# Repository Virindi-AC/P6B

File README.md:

# P6B
A Ramps-like printer board with 8 stepper drivers, 5 mosfets, and TMC2130 SPI.

By Jessica "Virindi" O.

pin_P6B.h is the pin configuration for Marlin.

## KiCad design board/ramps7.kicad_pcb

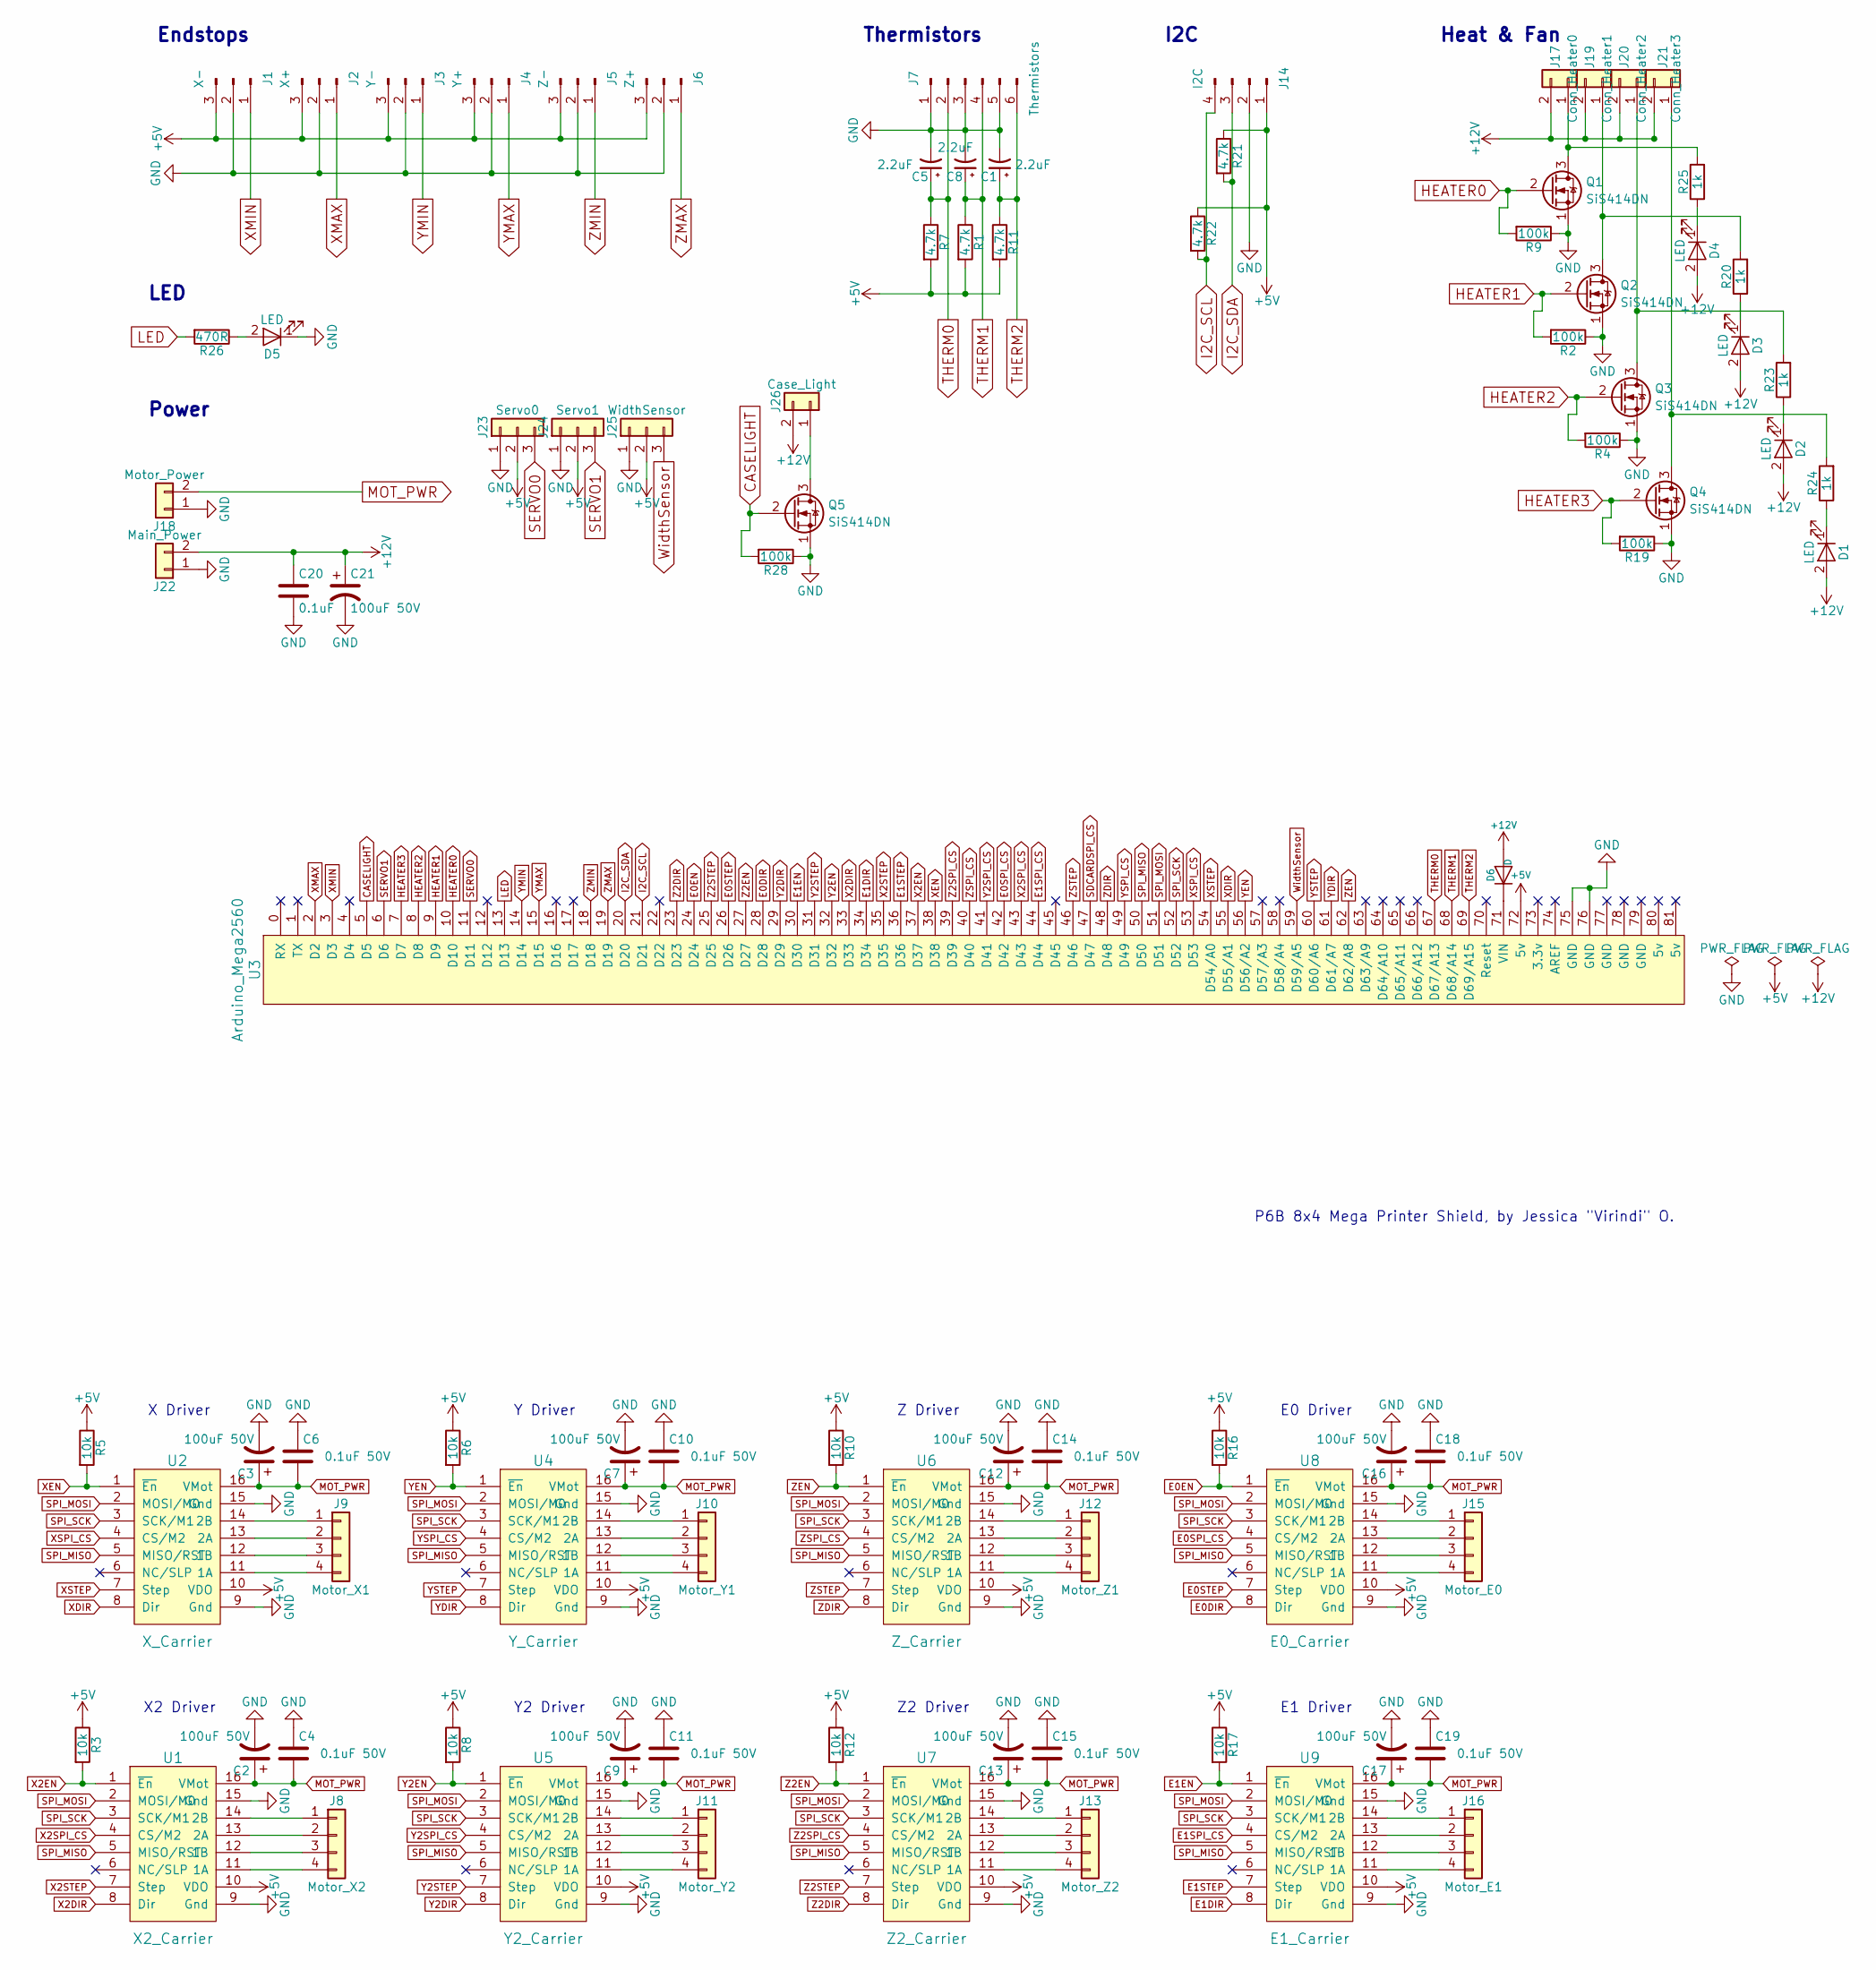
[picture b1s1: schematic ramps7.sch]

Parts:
C1, C5, C8: 2.2uF; C_0805
C2, C3, C7, C9, C12, C13, C16, C17, C21: 100uF 50V; CP_Elec_10x10.5
C4, C6, C10, C11, C14, C15, C18, C19: 0.1uF 50V; C_0805
C20: 0.1uF; C_0805
D1, D2, D3, D4, D5: LED; LED_0805
D6: D; D_DO-35_SOD27_P7.62mm_Horizontal
J1: X-; Pin_Header_Straight_1x03_Pitch2.54mm_SMD_Pin1Right
J2: X+; Pin_Header_Straight_1x03_Pitch2.54mm_SMD_Pin1Right
J3: Y-; Pin_Header_Straight_1x03_Pitch2.54mm_SMD_Pin1Right
J4: Y+; Pin_Header_Straight_1x03_Pitch2.54mm_SMD_Pin1Right
J5: Z-; Pin_Header_Straight_1x03_Pitch2.54mm_SMD_Pin1Right
J6: Z+; Pin_Header_Straight_1x03_Pitch2.54mm_SMD_Pin1Right
J7: Thermistors; Pin_Header_Straight_1x06_Pitch2.54mm_SMD_Pin1Left
J8: Motor_X2; Pin_Header_Straight_1x04_Pitch2.54mm_SMD_Pin1Right
J9: Motor_X1; Pin_Header_Straight_1x04_Pitch2.54mm_SMD_Pin1Right
J10: Motor_Y1; Pin_Header_Straight_1x04_Pitch2.54mm_SMD_Pin1Right
J11: Motor_Y2; Pin_Header_Straight_1x04_Pitch2.54mm_SMD_Pin1Right
J12: Motor_Z1; Pin_Header_Straight_1x04_Pitch2.54mm_SMD_Pin1Right
J13: Motor_Z2; Pin_Header_Straight_1x04_Pitch2.54mm_SMD_Pin1Right
J14: I2C; Pin_Header_Straight_1x04_Pitch2.54mm_SMD_Pin1Right
J15: Motor_E0; Pin_Header_Straight_1x04_Pitch2.54mm_SMD_Pin1Right
J16: Motor_E1; Pin_Header_Straight_1x04_Pitch2.54mm_SMD_Pin1Right
J17: Conn_Heater0; XT60_Land_THT
J18: Motor_Power; XT60_Land_THT
J19: Conn_Heater1; XT60_Land_THT
J20: Conn_Heater2; XT60_Land_THT
J21: Conn_Heater3; XT60_Land_THT
J22: Main_Power; XT60_Land_THT
J23: Servo0; Pin_Header_Straight_1x03_Pitch2.54mm_SMD_Pin1Right
J24: Servo1; Pin_Header_Straight_1x03_Pitch2.54mm_SMD_Pin1Right
J25: WidthSensor; Pin_Header_Straight_1x03_Pitch2.54mm_SMD_Pin1Right
J26: Case_Light; Pin_Header_Straight_1x02_Pitch2.54mm_SMD_Pin1Right
Q1, Q2, Q3, Q4, Q5: SiS414DN; PowerPAK_1212_8_Single
R1, R7, R11, R21, R22: 4.7k; R_0805
R2, R4, R9, R19, R28: 100k; R_0805
R3, R5, R6, R8, R10, R12, R16, R17: 10k; R_0805
R20, R23, R24, R25: 1k; R_0805
R26: 470R; R_0805
U1: X2_Carrier; TMC2130_Carrier_SMD
U2: X_Carrier; TMC2130_Carrier_SMD
U3: Arduino_Mega2560; ARDUINO_MEGA_SHIELD_R7_SMD
U4: Y_Carrier; TMC2130_Carrier_SMD
U5: Y2_Carrier; TMC2130_Carrier_SMD
U6: Z_Carrier; TMC2130_Carrier_SMD
U7: Z2_Carrier; TMC2130_Carrier_SMD
U8: E0_Carrier; TMC2130_Carrier_SMD
U9: E1_Carrier; TMC2130_Carrier_SMD

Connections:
+5V: J1.3, J2.3, J3.3, J4.3, J5.3, J6.3, J14.1, J23.2, J24.2, J25.2, R1.2, R3.1, R5.1, R6.1, R7.2, R8.1, R10.1, R11.2, R12.1, R16.1, R17.1, R21.1, R22.1, U1.10 (VDO), U2.10 (VDO), U3.72 (5v), U4.10 (VDO), U5.10 (VDO), U6.10 (VDO), U7.10 (VDO), U8.10 (VDO), U9.10 (VDO)
+12V: C20.1, C21.1, D1.2 (A), D2.2 (A), D3.2 (A), D4.2 (A), D6.2 (A), J17.2, J19.2, J20.2, J21.2, J22.2, J26.2
CASELIGHT: Q5.2 (G), R28.2, U3.5 (D5)
E0DIR: U3.28 (D28), U8.8 (Dir)
E0EN: R16.2, U3.24 (D24), U8.1 (~En)
E0SPI_CS: U3.42 (D42), U8.4 (CS/M2)
E0STEP: U3.26 (D26), U8.7 (Step)
E1DIR: U3.34 (D34), U9.8 (Dir)
E1EN: R17.2, U3.30 (D30), U9.1 (~En)
E1SPI_CS: U3.44 (D44), U9.4 (CS/M2)
E1STEP: U3.36 (D36), U9.7 (Step)
GND: C1.2, C2.2, C3.2, C4.1, C5.2, C6.1, C7.2, C8.2, C9.2, C10.1, C11.1, C12.2, C13.2, C14.1, C15.1, C16.2, C17.2, C18.1, C19.1, C20.2, C21.2, D5.1 (K), J1.2, J2.2, J3.2, J4.2, J5.2, J6.2, J7.1, J7.3, J7.5, J14.2, J18.1, J22.1, J23.1, J24.1, J25.1, Q1.1 (S), Q2.1 (S), Q3.1 (S), Q4.1 (S), Q5.1 (S), R2.1, R4.1, R9.1, R19.1, R28.1, U1.9 (Gnd), U1.15 (Gnd), U2.9 (Gnd), U2.15 (Gnd), U3.75 (GND), U3.76 (GND), U4.9 (Gnd), U4.15 (Gnd), U5.9 (Gnd), U5.15 (Gnd), U6.9 (Gnd), U6.15 (Gnd), U7.9 (Gnd), U7.15 (Gnd), U8.9 (Gnd), U8.15 (Gnd), U9.9 (Gnd), U9.15 (Gnd)
HEATER0: Q1.2 (G), R9.2, U3.10 (D10)
HEATER1: Q2.2 (G), R2.2, U3.9 (D9)
HEATER2: Q3.2 (G), R4.2, U3.8 (D8)
HEATER3: Q4.2 (G), R19.2, U3.7 (D7)
I2C_SCL: J14.4, R22.2, U3.21 (D21)
I2C_SDA: J14.3, R21.2, U3.20 (D20)
LED: R26.2, U3.13 (D13)
MOT_PWR: C2.1, C3.1, C4.2, C6.2, C7.1, C9.1, C10.2, C11.2, C12.1, C13.1, C14.2, C15.2, C16.1, C17.1, C18.2, C19.2, J18.2, U1.16 (VMot), U2.16 (VMot), U4.16 (VMot), U5.16 (VMot), U6.16 (VMot), U7.16 (VMot), U8.16 (VMot), U9.16 (VMot)
unnamed: D1.1 (K), R24.1
unnamed: D2.1 (K), R23.1
unnamed: D3.1 (K), R20.1
unnamed: D4.1 (K), R25.1
unnamed: D5.2 (A), R26.1
unnamed: D6.1 (K), U3.71 (VIN)
unnamed: J8.1, U1.14 (2B)
unnamed: J8.2, U1.13 (2A)
unnamed: J8.3, U1.12 (1B)
unnamed: J8.4, U1.11 (1A)
unnamed: J9.1, U2.14 (2B)
unnamed: J9.2, U2.13 (2A)
unnamed: J9.3, U2.12 (1B)
unnamed: J9.4, U2.11 (1A)
unnamed: J10.1, U4.14 (2B)
unnamed: J10.2, U4.13 (2A)
unnamed: J10.3, U4.12 (1B)
unnamed: J10.4, U4.11 (1A)
unnamed: J11.1, U5.14 (2B)
unnamed: J11.2, U5.13 (2A)
unnamed: J11.3, U5.12 (1B)
unnamed: J11.4, U5.11 (1A)
unnamed: J12.1, U6.14 (2B)
unnamed: J12.2, U6.13 (2A)
unnamed: J12.3, U6.12 (1B)
unnamed: J12.4, U6.11 (1A)
unnamed: J13.1, U7.14 (2B)
unnamed: J13.2, U7.13 (2A)
unnamed: J13.3, U7.12 (1B)
unnamed: J13.4, U7.11 (1A)
unnamed: J15.1, U8.14 (2B)
unnamed: J15.2, U8.13 (2A)
unnamed: J15.3, U8.12 (1B)
unnamed: J15.4, U8.11 (1A)
unnamed: J16.1, U9.14 (2B)
unnamed: J16.2, U9.13 (2A)
unnamed: J16.3, U9.12 (1B)
unnamed: J16.4, U9.11 (1A)
unnamed: J17.1, Q1.3 (D), R25.2
unnamed: J19.1, Q2.3 (D), R20.2
unnamed: J20.1, Q3.3 (D), R23.2
unnamed: J21.1, Q4.3 (D), R24.2
unnamed: J26.1, Q5.3 (D)
SDCARDSPI_CS: U3.47 (D47)
SERVO0: J23.3, U3.11 (D11)
SERVO1: J24.3, U3.6 (D6)
SPI_MISO: U1.5 (MISO/RST), U2.5 (MISO/RST), U3.50 (D50), U4.5 (MISO/RST), U5.5 (MISO/RST), U6.5 (MISO/RST), U7.5 (MISO/RST), U8.5 (MISO/RST), U9.5 (MISO/RST)
SPI_MOSI: U1.2 (MOSI/M0), U2.2 (MOSI/M0), U3.51 (D51), U4.2 (MOSI/M0), U5.2 (MOSI/M0), U6.2 (MOSI/M0), U7.2 (MOSI/M0), U8.2 (MOSI/M0), U9.2 (MOSI/M0)
SPI_SCK: U1.3 (SCK/M1), U2.3 (SCK/M1), U3.52 (D52), U4.3 (SCK/M1), U5.3 (SCK/M1), U6.3 (SCK/M1), U7.3 (SCK/M1), U8.3 (SCK/M1), U9.3 (SCK/M1)
THERM0: C5.1, J7.2, R7.1, U3.67 (D67/A13)
THERM1: C8.1, J7.4, R1.1, U3.68 (D68/A14)
THERM2: C1.1, J7.6, R11.1, U3.69 (D69/A15)
WidthSensor: J25.3, U3.59 (D59/A5)
X2DIR: U1.8 (Dir), U3.33 (D33)
X2EN: R3.2, U1.1 (~En), U3.37 (D37)
X2SPI_CS: U1.4 (CS/M2), U3.43 (D43)
X2STEP: U1.7 (Step), U3.35 (D35)
XDIR: U2.8 (Dir), U3.55 (D55/A1)
XEN: R5.2, U2.1 (~En), U3.38 (D38)
XMAX: J2.1, U3.2 (D2)
XMIN: J1.1, U3.3 (D3)
XSPI_CS: U2.4 (CS/M2), U3.53 (D53)
XSTEP: U2.7 (Step), U3.54 (D54/A0)
Y2DIR: U3.29 (D29), U5.8 (Dir)
Y2EN: R8.2, U3.32 (D32), U5.1 (~En)
Y2SPI_CS: U3.41 (D41), U5.4 (CS/M2)
Y2STEP: U3.31 (D31), U5.7 (Step)
YDIR: U3.61 (D61/A7), U4.8 (Dir)
YEN: R6.2, U3.56 (D56/A2), U4.1 (~En)
YMAX: J4.1, U3.15 (D15)
YMIN: J3.1, U3.14 (D14)
YSPI_CS: U3.49 (D49), U4.4 (CS/M2)
YSTEP: U3.60 (D60/A6), U4.7 (Step)
Z2DIR: U3.23 (D23), U7.8 (Dir)
Z2EN: R12.2, U3.27 (D27), U7.1 (~En)
Z2SPI_CS: U3.39 (D39), U7.4 (CS/M2)
Z2STEP: U3.25 (D25), U7.7 (Step)
ZDIR: U3.48 (D48), U6.8 (Dir)
ZEN: R10.2, U3.62 (D62/A8), U6.1 (~En)
ZMAX: J6.1, U3.19 (D19)
ZMIN: J5.1, U3.18 (D18)
ZSPI_CS: U3.40 (D40), U6.4 (CS/M2)
ZSTEP: U3.46 (D46), U6.7 (Step)

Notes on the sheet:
Heat & Fan
I2C
Thermistors
Endstops
X Driver
X2 Driver
Y Driver
Y2 Driver
Z Driver
Z2 Driver
E0 Driver
E1 Driver
LED
Power
P6B 8x4 Mega Printer Shield, by Jessica "Virindi" O.

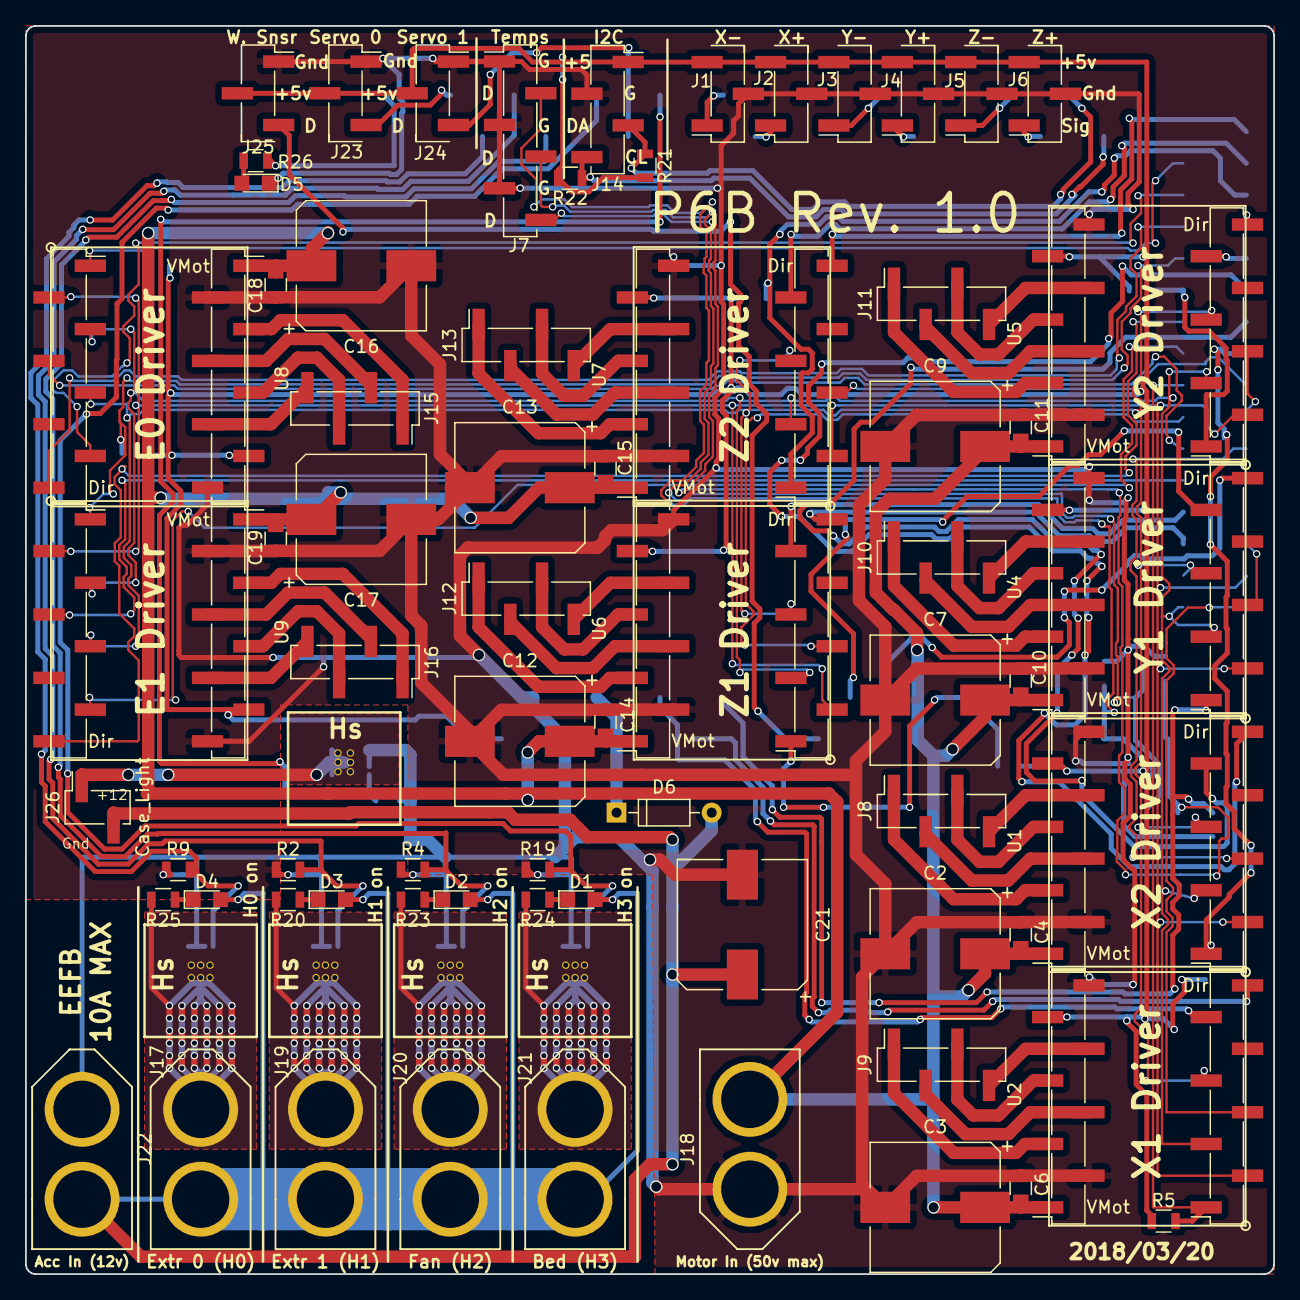
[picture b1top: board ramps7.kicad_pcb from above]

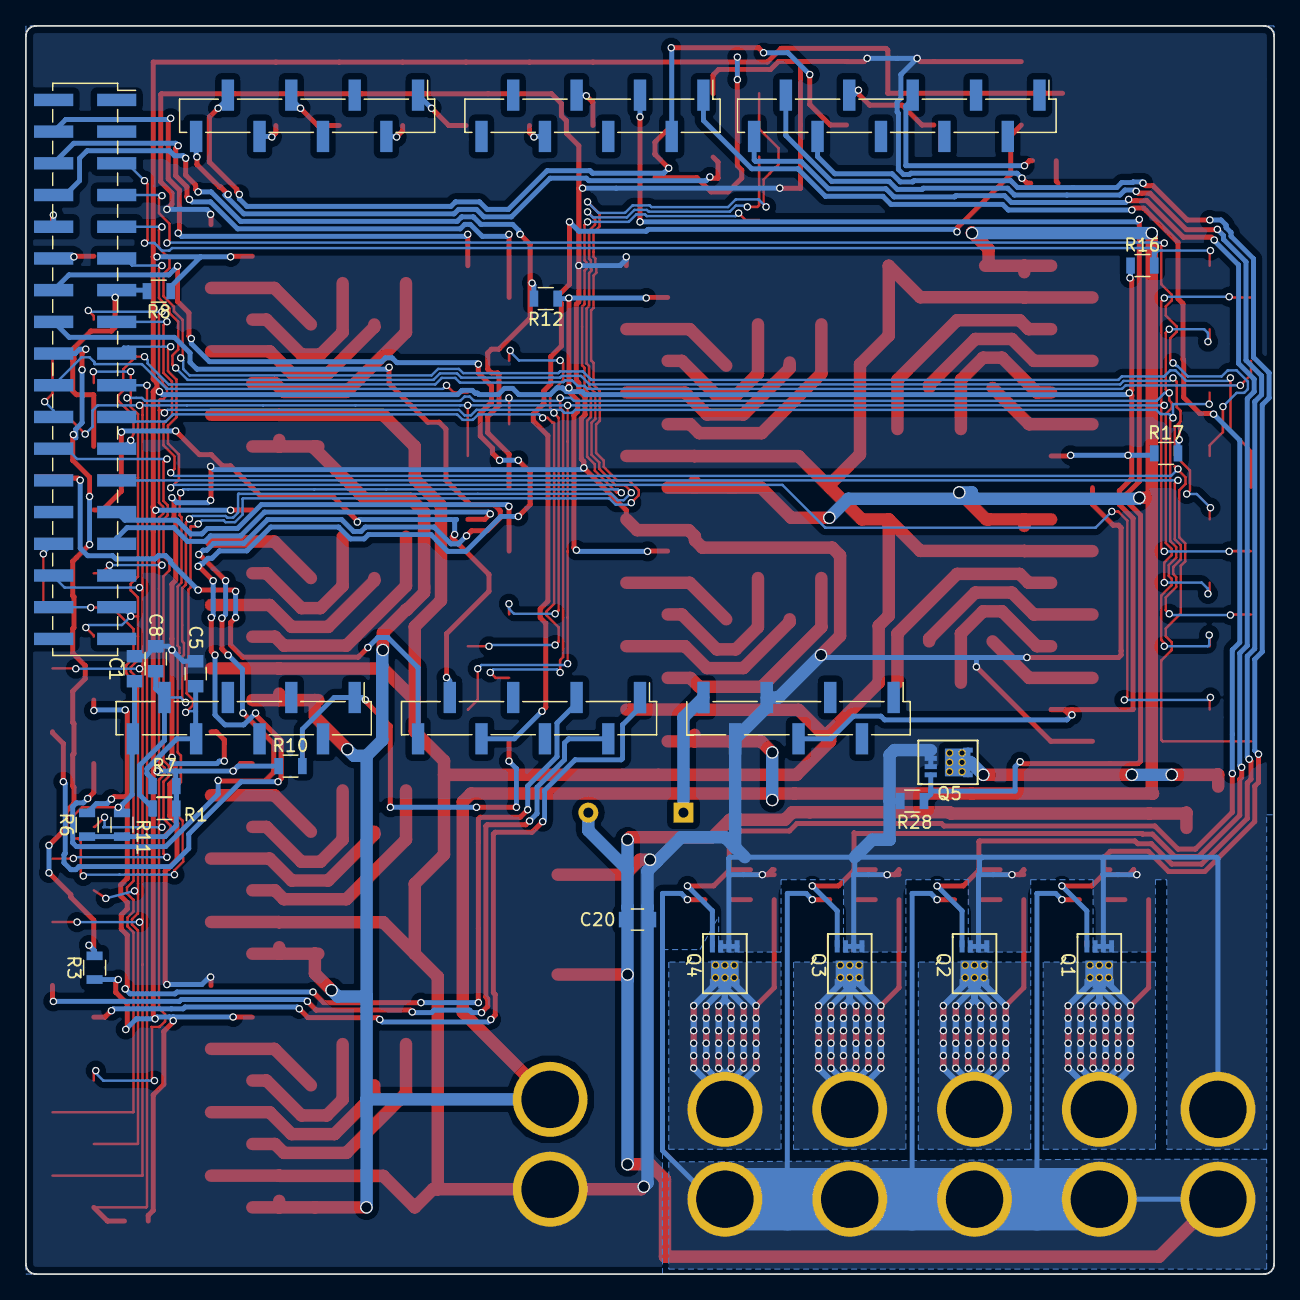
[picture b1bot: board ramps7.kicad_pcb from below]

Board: 2 copper layers, 100.0 x 100.0 mm, 90 parts (21 on the bottom side), 102 nets.
